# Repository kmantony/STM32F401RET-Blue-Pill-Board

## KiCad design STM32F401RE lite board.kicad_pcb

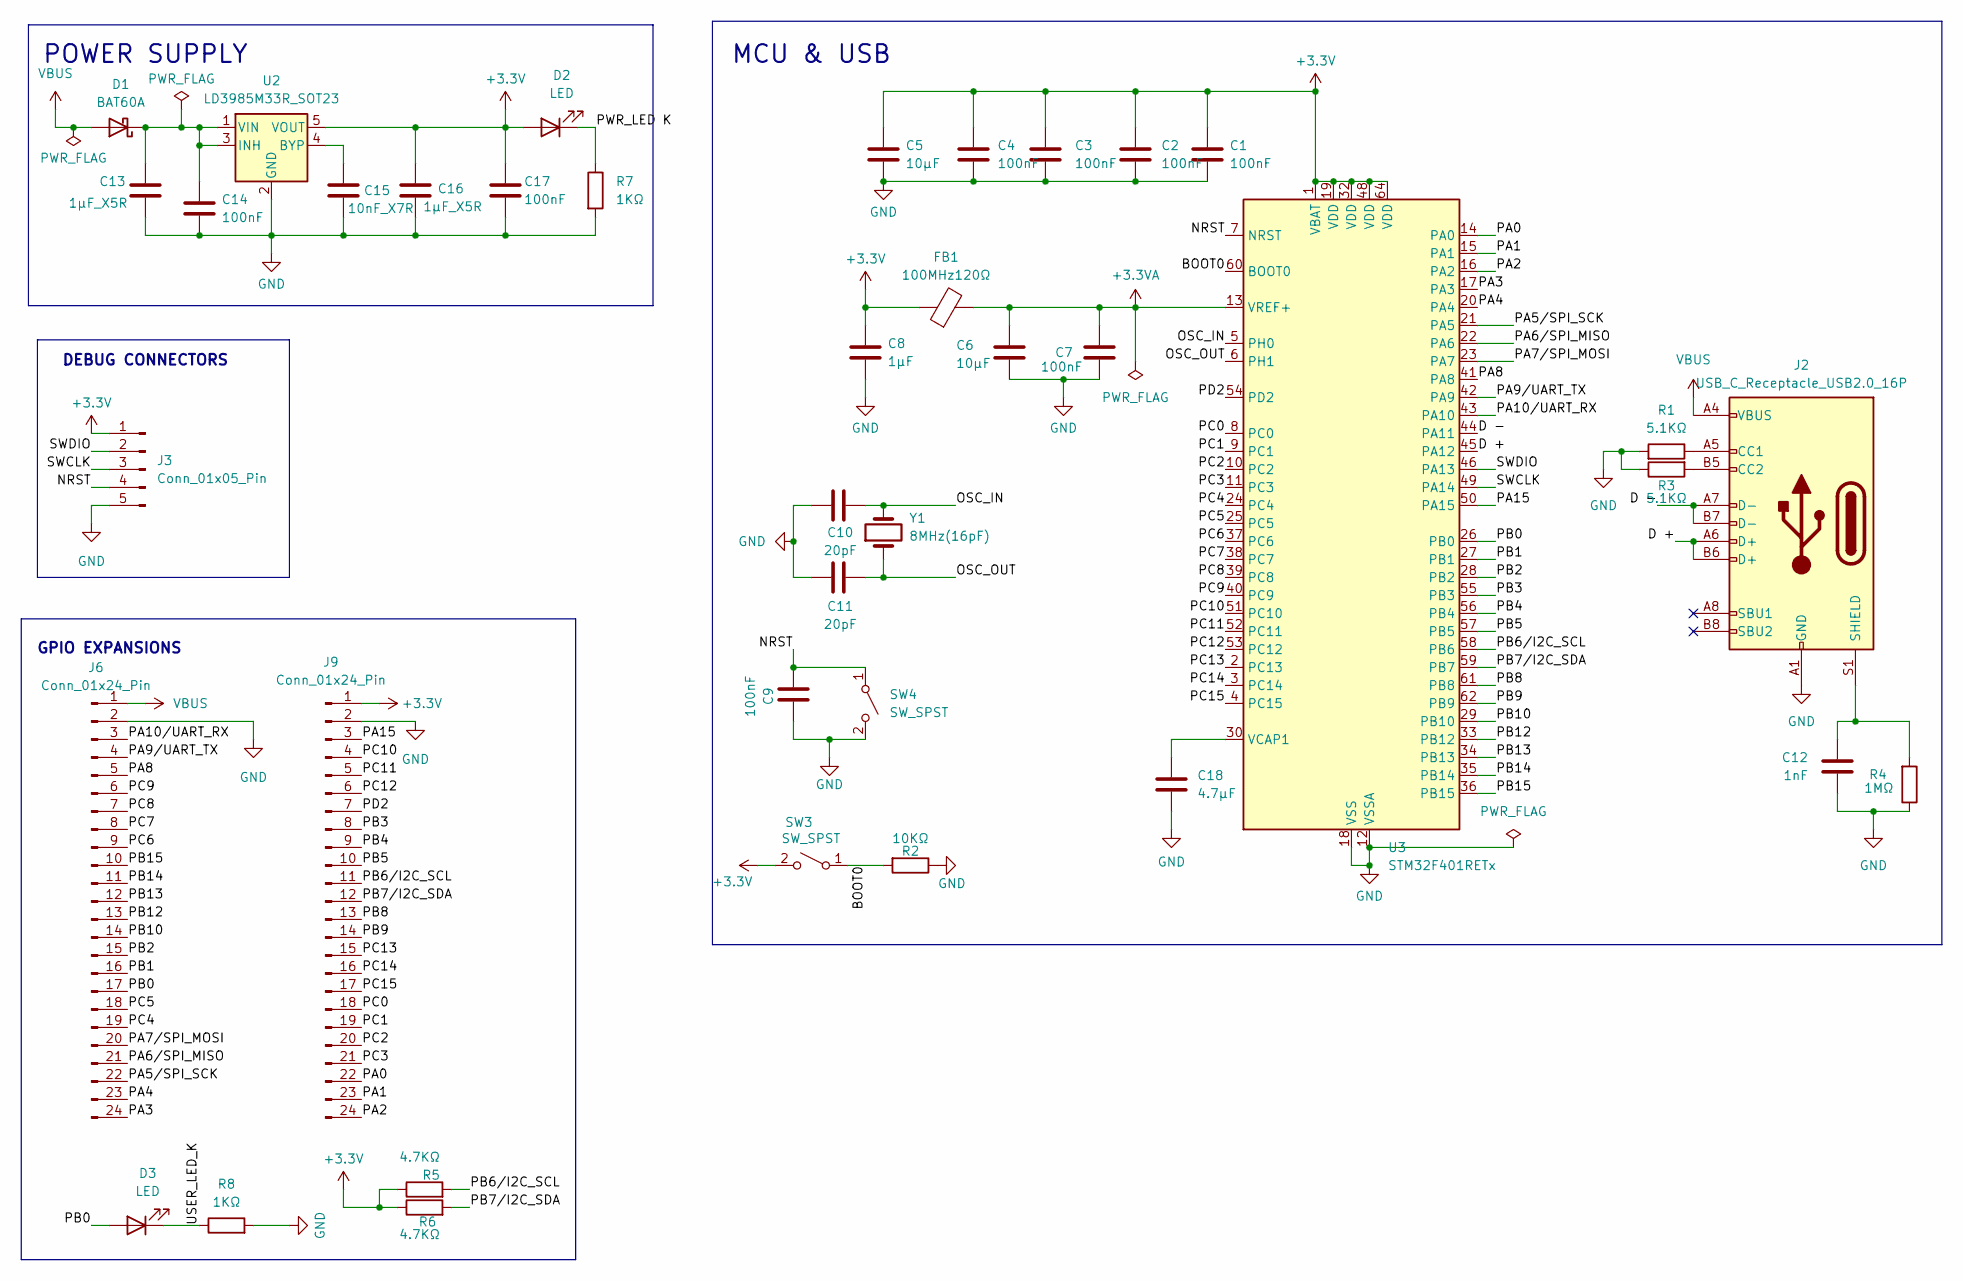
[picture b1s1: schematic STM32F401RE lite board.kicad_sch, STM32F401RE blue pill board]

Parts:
C1, C2, C3, C4, C7, C17: 100nF; C_0402_1005Metric
C5, C6: 10µF; C_0805_2012Metric
C8: 1µF; C_0402_1005Metric
C9, C14: 100nF; C_0603_1608Metric
C10, C11: 20pF; C_0402_1005Metric
C12: 1nF; C_0402_1005Metric
C13, C16: 1µF_X5R; C_0402_1005Metric
C15: 10nF_X7R; C_0402_1005Metric
C18: 4.7µF; C_0805_2012Metric
D1: BAT60A; D_SOD-323
D2, D3: LED; LED_0603_1608Metric
FB1: 100MHz120Ω; L_0603_1608Metric
J2: USB_C_Receptacle_USB2.0_16P; USB_C_Receptacle_HRO_TYPE-C-31-M-12
J3: Conn_01x05_Pin; PinHeader_1x05_P2.54mm_Vertical
J6, J9: Conn_01x24_Pin; PinHeader_1x24_P2.54mm_Vertical
R1, R3: 5.1KΩ; R_0402_1005Metric
R2: 10KΩ; R_0402_1005Metric
R4: 1MΩ; R_0402_1005Metric
R5, R6: 4.7KΩ; R_0402_1005Metric
R7, R8: 1KΩ; R_0402_1005Metric
SW3, SW4: SW_SPST; SW_SPST_TL3342
U2: LD3985M33R_SOT23; SOT-23-5
U3: STM32F401RETx; LQFP-64_10x10mm_P0.5mm
Y1: 8MHz(16pF); Crystal_HC49-4H_Vertical

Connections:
+3.3V: C1.1, C2.1, C3.1, C4.1, C5.1, C8.1, C16.1, C17.1, D2.2 (A), FB1.1, J3.1, J9.1, R5.1, R6.1, SW3.2 (B), U2.5 (VOUT), U3.1 (VBAT), U3.19 (VDD), U3.32 (VDD), U3.48 (VDD), U3.64 (VDD)
+3.3VA: C6.1, C7.1, FB1.2, U3.13 (VREF+)
/BOOT0: R2.2, SW3.1 (A), U3.60 (BOOT0)
/D +: J2.A6 (D+), J2.B6 (D+), U3.45 (PA12)
/D -: J2.A7 (D-), J2.B7 (D-), U3.44 (PA11)
/NRST: C9.2, J3.4, SW4.1 (A), U3.7 (NRST)
/OSC_IN: C10.2, U3.5 (PH0), Y1.2
/OSC_OUT: C11.2, U3.6 (PH1), Y1.1
/PA0: J9.22, U3.14 (PA0)
/PA1: J9.23, U3.15 (PA1)
/PA2: J9.24, U3.16 (PA2)
/PA3: J6.24, U3.17 (PA3)
/PA4: J6.23, U3.20 (PA4)
/PA5/SPI_SCK: J6.22, U3.21 (PA5)
/PA6/SPI_MISO: J6.21, U3.22 (PA6)
/PA7/SPI_MOSI: J6.20, U3.23 (PA7)
/PA8: J6.5, U3.41 (PA8)
/PA9/UART_TX: J6.4, U3.42 (PA9)
/PA10/UART_RX: J6.3, U3.43 (PA10)
/PA15: J9.3, U3.50 (PA15)
/PB0: D3.2 (A), J6.17, U3.26 (PB0)
/PB1: J6.16, U3.27 (PB1)
/PB2: J6.15, U3.28 (PB2)
/PB3: J9.8, U3.55 (PB3)
/PB4: J9.9, U3.56 (PB4)
/PB5: J9.10, U3.57 (PB5)
/PB6/I2C_SCL: J9.11, R5.2, U3.58 (PB6)
/PB7/I2C_SDA: J9.12, R6.2, U3.59 (PB7)
/PB8: J9.13, U3.61 (PB8)
/PB9: J9.14, U3.62 (PB9)
/PB10: J6.14, U3.29 (PB10)
/PB12: J6.13, U3.33 (PB12)
/PB13: J6.12, U3.34 (PB13)
/PB14: J6.11, U3.35 (PB14)
/PB15: J6.10, U3.36 (PB15)
/PC0: J9.18, U3.8 (PC0)
/PC1: J9.19, U3.9 (PC1)
/PC2: J9.20, U3.10 (PC2)
/PC3: J9.21, U3.11 (PC3)
/PC4: J6.19, U3.24 (PC4)
/PC5: J6.18, U3.25 (PC5)
/PC6: J6.9, U3.37 (PC6)
/PC7: J6.8, U3.38 (PC7)
/PC8: J6.7, U3.39 (PC8)
/PC9: J6.6, U3.40 (PC9)
/PC10: J9.4, U3.51 (PC10)
/PC11: J9.5, U3.52 (PC11)
/PC12: J9.6, U3.53 (PC12)
/PC13: J9.15, U3.2 (PC13)
/PC14: J9.16, U3.3 (PC14)
/PC15: J9.17, U3.4 (PC15)
/PD2: J9.7, U3.54 (PD2)
/PWR_LED K: D2.1 (K), R7.1
/SWCLK: J3.3, U3.49 (PA14)
/SWDIO: J3.2, U3.46 (PA13)
/USER_LED_K: D3.1 (K), R8.1
GND: C1.2, C2.2, C3.2, C4.2, C5.2, C6.2, C7.2, C8.2, C9.1, C10.1, C11.1, C12.2, C13.2, C14.2, C15.2, C16.2, C17.2, C18.2, J2.A1 (GND), J2.A12 (GND), J2.B1 (GND), J2.B12 (GND), J3.5, J6.2, J9.2, R1.2, R2.1, R3.1, R4.1, R7.2, R8.2, SW4.2 (B), U2.2 (GND), U3.12 (VSSA), U3.18 (VSS), U3.31 (VSS), U3.47 (VSS), U3.63 (VSS)
unnamed: C13.1, C14.1, D1.1 (K), U2.1 (VIN), U2.3 (INH)
unnamed: J2.A5 (CC1), R1.1
unnamed: J2.B5 (CC2), R3.2
unnamed: C12.1, J2.S1 (SHIELD), R4.2
unnamed: C15.1, U2.4 (BYP)
unnamed: C18.1, U3.30 (VCAP1)
VBUS: D1.2 (A), J2.A4 (VBUS), J2.A9 (VBUS), J2.B4 (VBUS), J2.B9 (VBUS), J6.1

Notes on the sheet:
DEBUG CONNECTORS
POWER SUPPLY
GPIO EXPANSIONS
MCU & USB

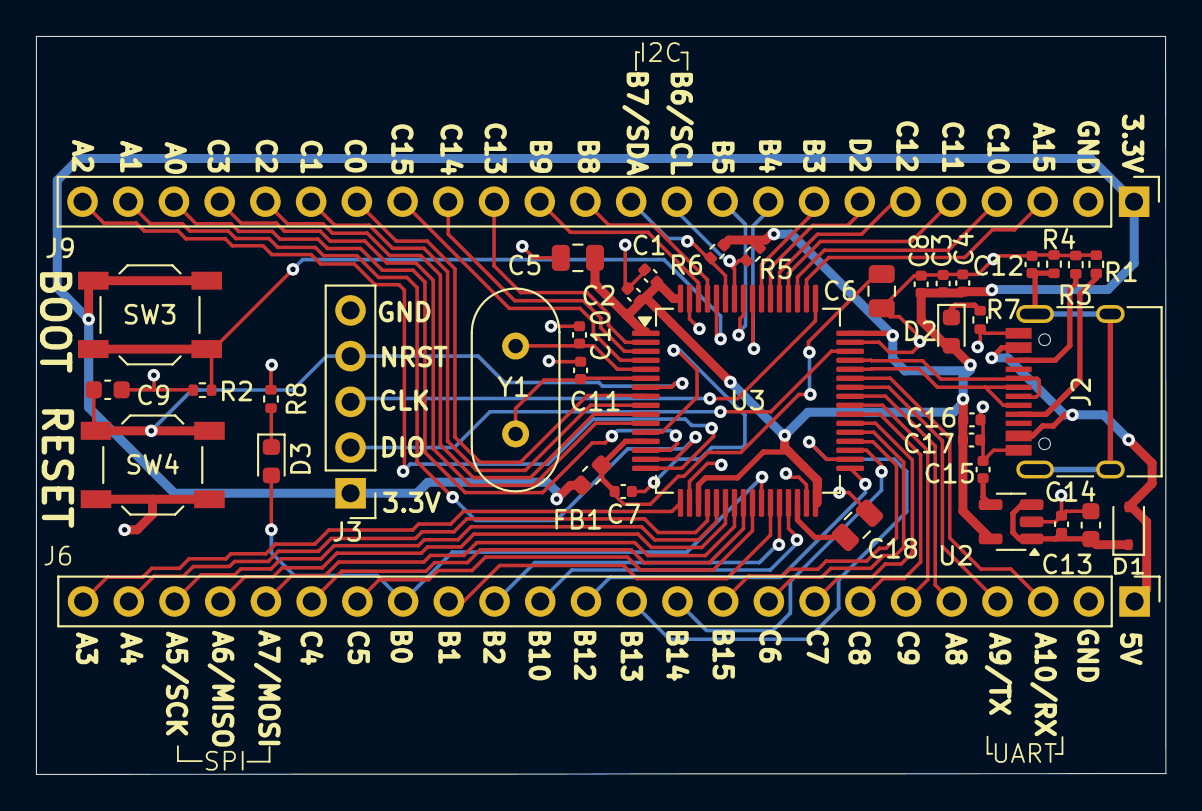
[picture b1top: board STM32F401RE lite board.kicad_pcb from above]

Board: 2 copper layers, 62.8 x 41.0 mm, 39 parts (0 on the bottom side), 64 nets.
